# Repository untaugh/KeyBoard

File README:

USB stick with AVR ATMega32u2 microcontroller

PCB designed in KiCad.
The code is for emulating a keyboard and typing a password from EEPROM when the button is pressed.
It uses the LUFA usb library.

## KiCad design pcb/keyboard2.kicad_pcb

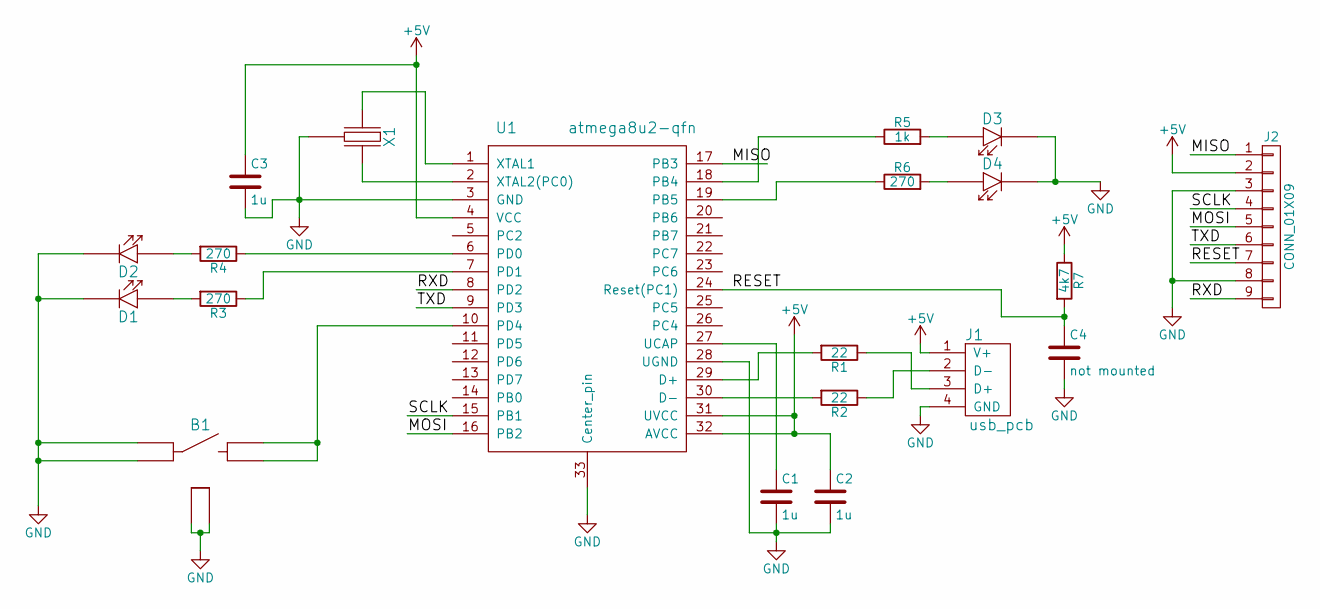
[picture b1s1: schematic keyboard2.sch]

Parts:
B1: btn_sp2; button_smd_panasonic; DigikeyPart P8045SCT-ND
C1, C2, C3: 1u; C_0402_nosilk; DigikeyPart 311-1702-1-ND
C4: not mounted; C_0402_nosilk; DigikeyPart 311-1335-1-ND
D1: led_red; LED_0603_nosilk; DigikeyPart 160-1446-1-ND
D2: led_green; LED_0603_nosilk; DigikeyPart 160-1447-1-ND
D3: led_blue; LED_0603_nosilk; DigikeyPart 160-1448-1-ND
D4: led_yellow; LED_0603_nosilk; DigikeyPart 160-1647-1-ND
J1: usb_pcb
J2: CONN_01X09; connector_smd_round2
R1, R2: 22; R_0402_nosilk; DigikeyPart 311-22.0LRCT-ND
R3, R4, R6: 270; R_0402_nosilk; DigikeyPart 311-270LRCT-ND
R5: 1k; R_0402_nosilk; DigikeyPart 311-1KLBCT-ND
R7: 4k7; R_0402_nosilk; DigikeyPart 311-4.7KLRCT-ND
U1: atmega8u2-qfn; qfn32_nosilk; DigikeyPart ATMEGA32U2-MURCT
X1: resonator; resonator_murata_smd; DigikeyPart 490-1219-1-ND

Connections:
+5V: C2.1, C3.1, J1.1 (V+), J2.2, R7.1, U1.4 (VCC), U1.31 (UVCC), U1.32 (AVCC)
/MISO: J2.1, U1.17 (PB3)
/MOSI: J2.5, U1.16 (PB2)
/RESET: C4.1, J2.7, R7.2, U1.24 (Reset(PC1))
/RXD: J2.9, U1.8 (PD2)
/SCLK: J2.4, U1.15 (PB1)
/TXD: J2.6, U1.9 (PD3)
GND: B1.1 (p1), B1.2 (p2), B1.5 (gnd), B1.6 (gnd), C1.2, C2.2, C3.2, C4.2, D1.2 (cathode), D2.2 (cathode), D3.2 (cathode), D4.2 (cathode), J1.4 (GND), J2.3, J2.8, U1.3 (GND), U1.28 (UGND), U1.33 (Center_pin), X1.2 (p2)
unnamed: B1.3 (p3), B1.4 (p4), U1.10 (PD4)
unnamed: C1.1, U1.27 (UCAP)
unnamed: D1.1 (anode), R3.2
unnamed: D2.1 (anode), R4.2
unnamed: D3.1 (anode), R5.2
unnamed: D4.1 (anode), R6.2
unnamed: J1.2 (D-), R2.1
unnamed: J1.3 (D+), R1.1
unnamed: R1.2, U1.29 (D+)
unnamed: R2.2, U1.30 (D-)
unnamed: R3.1, U1.7 (PD1)
unnamed: R4.1, U1.6 (PD0)
unnamed: R5.1, U1.18 (PB4)
unnamed: R6.1, U1.19 (PB5)
unnamed: U1.1 (XTAL1), X1.1 (p1)
unnamed: U1.2 (XTAL2(PC0)), X1.3 (p3)

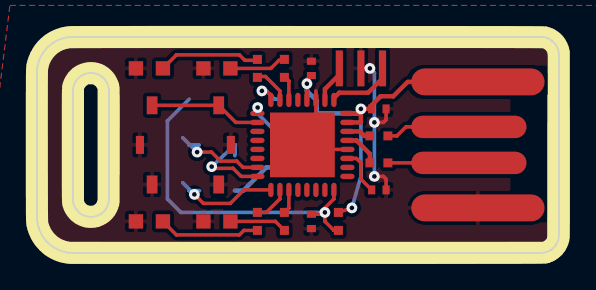
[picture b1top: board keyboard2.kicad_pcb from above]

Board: 2 copper layers, 29.0 x 12.0 mm, 20 parts (1 on the bottom side), 24 nets.

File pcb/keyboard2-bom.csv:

Date:,Mon 19 Oct 2015 10:09:02 PM CEST
Tool:,Eeschema (after 2015-mar-04 BZR unknown)-product
Ref,Qnty,Value,Cmp name,Footprint,Description,Vendor,Digikey Part
B1 ,1,btn_sp2,btn_sp2,oscu_footprints:button_smd_panasonic,,,P8045SCT-ND
C1 C2 C3 ,3,1u,C,oscu_footprints:C_0402_nosilk,Unpolarized capacitor,,311-1702-1-ND
C4 ,1,100n,C,oscu_footprints:C_0402_nosilk,Unpolarized capacitor,,311-1335-1-ND
D1 ,1,led_red,led1,oscu_footprints:LED_0603_nosilk,,,160-1446-1-ND
D2 ,1,led_green,led1,oscu_footprints:LED_0603_nosilk,,,160-1447-1-ND
D3 ,1,led_blue,led1,oscu_footprints:LED_0603_nosilk,,,160-1448-1-ND
D4 ,1,led_yellow,led1,oscu_footprints:LED_0603_nosilk,,,160-1647-1-ND
J1 ,1,usb_pcb,usb_pcb,oscu_footprints:usb_pcb,,,
J2 ,1,CONN_01X09,CONN_01X09,oscu_footprints:connector_smd_round2,,,
R1 R2 ,2,22,R,oscu_footprints:R_0402_nosilk,Resistor,,311-22.0LRCT-ND
R3 R4 R6 ,3,270,R,oscu_footprints:R_0402_nosilk,Resistor,,311-270LRCT-ND
R5 ,1,1k,R,oscu_footprints:R_0402_nosilk,Resistor,,311-1KLBCT-ND
R7 ,1,4k7,R,oscu_footprints:R_0402_nosilk,Resistor,,311-4.7KLRCT-ND
U1 ,1,atmega8u2-qfn,atmega8u2-qfn,oscu_footprints:qfn32_nosilk,,,ATMEGA32U2-MURCT
X1 ,1,resonator,resonator,oscu_footprints:resonator_murata_smd,,,490-1219-1-ND

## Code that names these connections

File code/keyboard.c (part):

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  STATE_RECONFIG, 
};

#define RED_LED PD1
#define GREEN_LED PD0
#define YELLOW_LED PB5
#define BLUE_LED PB4

// set and clear functions for leds
static void set_red(void)
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  
  GlobalInterruptEnable();

  PORTD |= _BV(PD4); // pull-up button

  // Setup Timer
  // prescaler
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    }

  // if button is up
  if (PIND & _BV(PD4))
    {
      // button was down previously
      if (button & _BV(BTN1_LONG))
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
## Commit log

2015-10-13 First commit of the seconds version.
2015-10-13 Added, moved and edited gitignorefiles.
2015-10-19 Edit resistor value.
2015-10-24 Schematic part changes.
2015-10-24 Changed pinout.
2015-11-07 Changed code for new pcb.
2015-11-07 A tool for holding stencil while applying paste.
2015-11-07 Updated stencilholder
2016-03-13 Fixed modulo bias in random generator.
2016-05-28 Included blinkmode in the project, instead of external library.
2016-05-28 Change manufacturer and product descriptors.
2016-05-28 fix product descriptor
2016-05-28 changed default password
2016-06-16 changed readme
2016-06-16 pinout png
2016-06-17 added and updated libraries
2016-06-17 update reset capacitor not mounted
2016-06-19 pinout top and bot
